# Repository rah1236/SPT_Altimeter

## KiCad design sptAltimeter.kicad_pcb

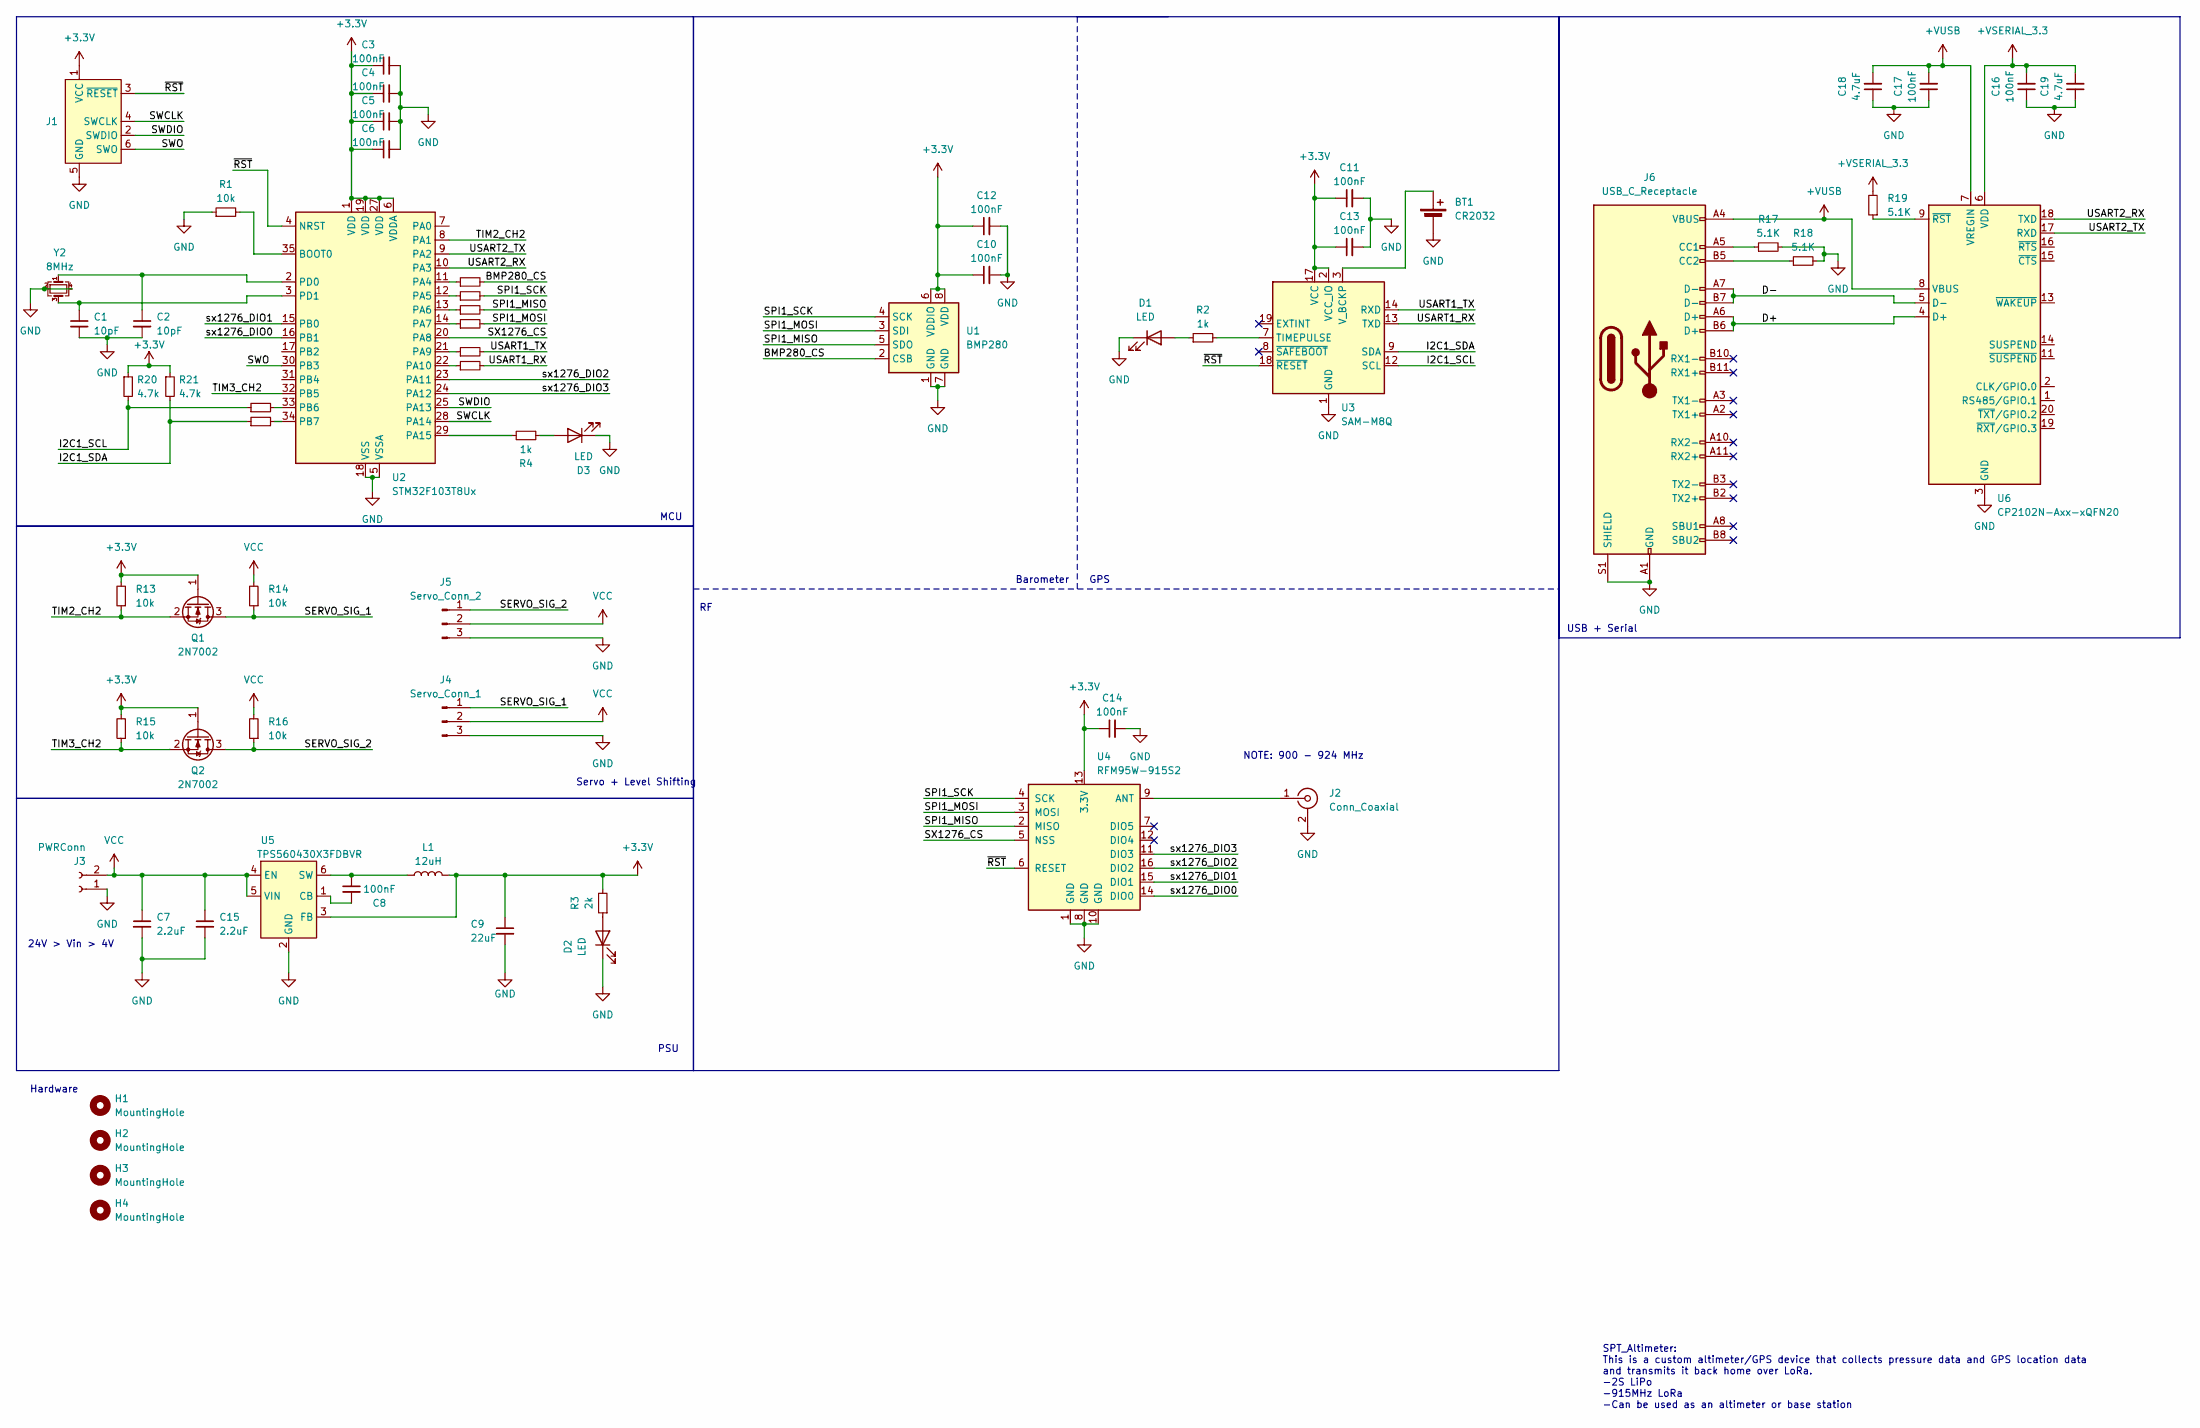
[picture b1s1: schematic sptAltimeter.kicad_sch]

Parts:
BT1: CR2032; BatteryHolder_Keystone_1060_1x2032
C1, C2: 10pF; C_0402_1005Metric; LCSC C650948
C3, C4, C5, C6, C8, C10, C11, C12, C13, C14, C16, C17: 100nF; C_0402_1005Metric
C7, C15: 2.2uF; C_0603_1608Metric
C9: 22uF; C_0402_1005Metric
C18, C19: 4.7uF; C_0402_1005Metric
D1, D2, D3: LED; LED_0603_1608Metric
H1, H2, H3, H4: MountingHole; MountingHole_3.2mm_M3
J1: Conn_ARM_SWD_TagConnect_TC2030-NL; Tag-Connect_TC2030-IDC-NL_2x03_P1.27mm_Vertical
J2: Conn_Coaxial; SMA_Amphenol_132289_EdgeMount
J3: PWRConn; AMASS_XT30PW-M_1x02_P2.50mm_Horizontal
J4: Servo_Conn_1; PinHeader_1x03_P2.54mm_Horizontal
J5: Servo_Conn_2; PinHeader_1x03_P2.54mm_Horizontal
J6: USB_C_Receptacle; USB_C_Receptacle_GCT_USB4105-xx-A_16P_TopMnt_Horizontal
L1: 12uH; L_1210_3225Metric
Q1: 2N7002; SOT-23
Q2: 2N7002; SOT-23; LCSC C3144321
R1, R13, R14, R15, R16: 10k; R_0402_1005Metric
R2, R4: 1k; R_0402_1005Metric
R3: 2k; R_0402_1005Metric
R5, R6, R7, R8, R9, R10, R11, R12: 0; R_0402_1005Metric
R17, R18, R19: 5.1K; R_0603_1608Metric
R20, R21: 4.7k; R_0402_1005Metric
U1: BMP280; Bosch_LGA-8_2x2.5mm_P0.65mm_ClockwisePinNumbering
U2: STM32F103T8Ux; QFN-36-1EP_6x6mm_P0.5mm_EP4.1x4.1mm
U3: SAM-M8Q; ublox_SAM-M8Q
U4: RFM95W-915S2; XCVR_RFM95W-915S2
U5: TPS560430X3FDBVR; SOT-23-6
U6: CP2102N-Axx-xQFN20; SiliconLabs_QFN-20-1EP_3x3mm_P0.5mm_EP1.8x1.8mm
Y2: 8MHz; Crystal_SMD_3225-4Pin_3.2x2.5mm; LCSC C20606311

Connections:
+3.3V: C3.1, C4.1, C5.1, C6.1, C9.1, C10.1, C11.1, C12.1, C13.1, C14.1, J1.1 (VCC), L1.2, Q1.1 (G), Q2.1 (G), R3.2, R13.2, R15.2, R20.1, R21.1, U1.6 (VDDIO), U1.8 (VDD), U2.1 (VDD), U2.6 (VDDA), U2.19 (VDD), U2.27 (VDD), U3.2 (VCC_IO), U3.17 (VCC), U4.13 (3.3V), U5.3 (FB)
+VSERIAL_3.3: C16.2, C19.2, R19.2, U6.6 (VDD)
+VUSB: C17.2, C18.2, J6.A4 (VBUS), J6.A9 (VBUS), J6.B4 (VBUS), J6.B9 (VBUS), U6.7 (VREGIN), U6.8 (VBUS)
/BMP280_CS: R12.2, U1.2 (CSB)
/D+: J6.A6 (D+), J6.B6 (D+), U6.4 (D+)
/D-: J6.A7 (D-), J6.B7 (D-), U6.5 (D-)
/I2C1_SCL: R6.1, R20.2, U3.12 (SCL)
/I2C1_SDA: R5.1, R21.2, U3.9 (SDA)
/SERVO_SIG_1: J4.1, Q1.3 (D), R14.1
/SERVO_SIG_2: J5.1, Q2.3 (D), R16.1
/SPI1_MISO: R10.2, U1.5 (SDO), U4.2 (MISO)
/SPI1_MOSI: R9.2, U1.3 (SDI), U4.3 (MOSI)
/SPI1_SCK: R11.2, U1.4 (SCK), U4.4 (SCK)
/SWCLK: J1.4 (SWCLK), U2.28 (PA14)
/SWDIO: J1.2 (SWDIO), U2.25 (PA13)
/SWO: J1.6 (SWO), U2.30 (PB3)
/SX1276_CS: U2.20 (PA8), U4.5 (NSS)
/TIM2_CH2: Q1.2 (S), R13.1, U2.8 (PA1)
/TIM3_CH2: Q2.2 (S), R15.1, U2.32 (PB5)
/USART1_RX: R7.2, U3.13 (TXD)
/USART1_TX: R8.2, U3.14 (RXD)
/USART2_RX: U2.10 (PA3), U6.18 (TXD)
/USART2_TX: U2.9 (PA2), U6.17 (RXD)
/sx1276_DIO0: U2.16 (PB1), U4.14 (DIO0)
/sx1276_DIO1: U2.15 (PB0), U4.15 (DIO1)
/sx1276_DIO2: U2.23 (PA11), U4.16 (DIO2)
/sx1276_DIO3: U2.24 (PA12), U4.11 (DIO3)
/~RST: J1.3 (~RESET), U2.4 (NRST), U3.18 (~RESET), U4.6 (RESET)
GND: BT1.2 (-), C1.2, C2.2, C3.2, C4.2, C5.2, C6.2, C7.2, C9.2, C10.2, C11.2, C12.2, C13.2, C14.2, C15.2, C16.1, C17.1, C18.1, C19.1, D1.1 (K), D2.1 (K), D3.1 (K), J1.5 (GND), J2.2 (Ext), J3.1, J4.3, J5.3, J6.A1 (GND), J6.A12 (GND), J6.B1 (GND), J6.B12 (GND), J6.S1 (SHIELD), R1.1, R17.2, R18.2, U1.1 (GND), U1.7 (GND), U2.5 (VSSA), U2.18 (VSS), U2.26 (VSS), U2.36 (VSS), U2.37 (VSS), U3.1 (GND), U3.4 (GND), U3.5 (GND), U3.6 (GND), U3.10 (GND), U3.11 (GND), U3.15 (GND), U3.16 (GND), U3.20 (GND), U4.1 (GND), U4.8 (GND), U4.10 (GND), U5.2 (GND), U6.3 (GND), U6.12 (GND), U6.21 (GND), Y2.2, Y2.4
unnamed: BT1.1 (+), U3.3 (V_BCKP)
unnamed: D1.2 (A), R2.1
unnamed: D2.2 (A), R3.1
unnamed: D3.2 (A), R4.1
unnamed: J2.1 (In), U4.9 (ANT)
unnamed: J6.A5 (CC1), R17.1
unnamed: J6.B5 (CC2), R18.1
unnamed: R1.2, U2.35 (BOOT0)
unnamed: R12.1, U2.11 (PA4)
unnamed: R11.1, U2.12 (PA5)
unnamed: R10.1, U2.13 (PA6)
unnamed: R9.1, U2.14 (PA7)
unnamed: R8.1, U2.21 (PA9)
unnamed: R7.1, U2.22 (PA10)
unnamed: R4.2, U2.29 (PA15)
unnamed: R6.2, U2.33 (PB6)
unnamed: R5.2, U2.34 (PB7)
unnamed: C2.1, U2.2 (PD0), Y2.1
unnamed: C1.1, U2.3 (PD1), Y2.3
unnamed: R2.2, U3.7 (TIMEPULSE)
unnamed: C8.2, U5.1 (CB)
unnamed: C8.1, L1.1, U5.6 (SW)
unnamed: R19.1, U6.9 (~RST)
VCC: C7.1, C15.1, J3.2, J4.2, J5.2, R14.2, R16.2, U5.4 (EN), U5.5 (VIN)

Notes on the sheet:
MCU
SPT_Altimeter: This is a custom altimeter/GPS device that collects pressure data and GPS location data and transmits it back home over LoRa. -2S LiPo -915MHz LoRa -Can be used as an altimeter or base station
PSU
24V > Vin > 4V
Barometer
GPS
Servo + Level Shifting
NOTE: 900 - 924 MHz
Hardware
USB + Serial

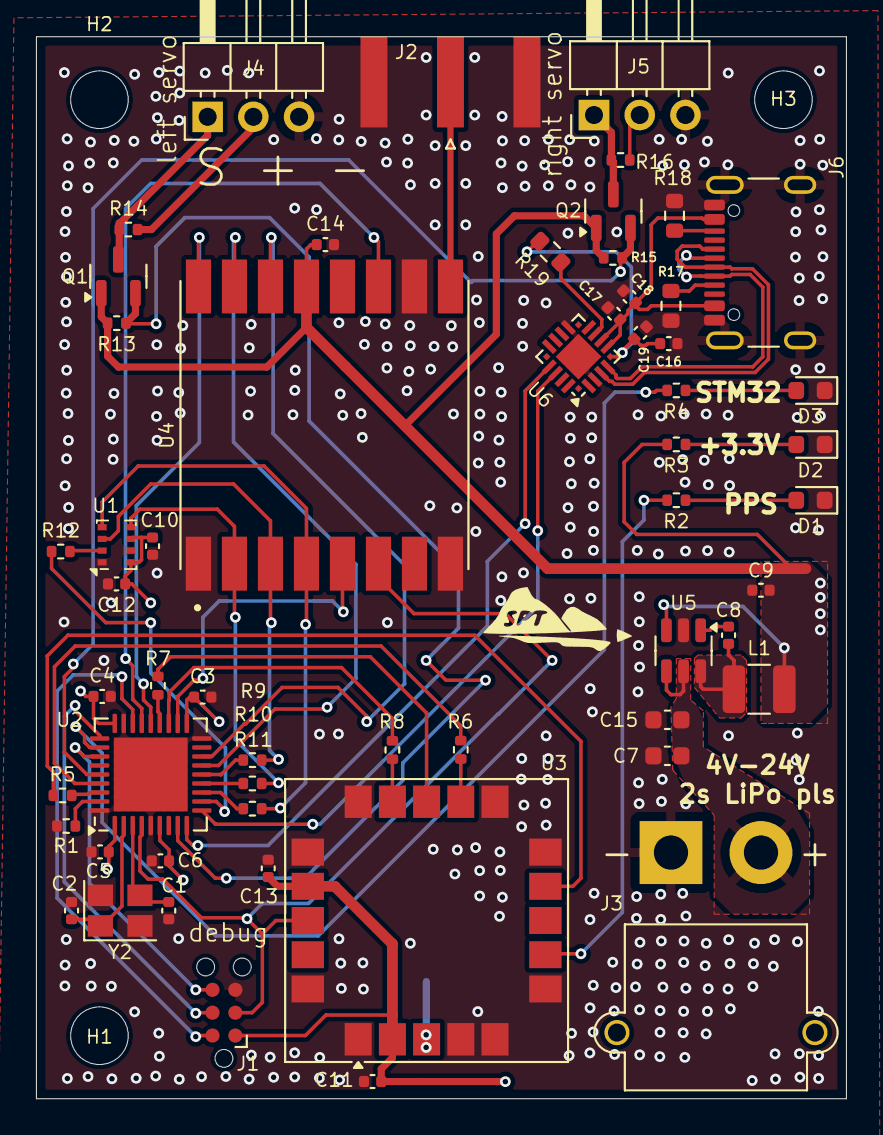
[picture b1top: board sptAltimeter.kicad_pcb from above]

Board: 4 copper layers, 45.0 x 59.0 mm, 61 parts (1 on the bottom side), 53 nets.

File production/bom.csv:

Designator,Footprint,Quantity,Value,LCSC Part #
BT1,BatteryHolder_Keystone_1060_1x2032,1,CR2032,
"C1, C2",0402,2,10pF,C650948
"C10, C11, C12, C13, C14, C16, C17, C3, C4, C5, C6, C8",0402,12,100nF,
"C15, C7",0603,2,2.2uF,
"C18, C19",0402,2,4.7uF,
C9,0402,1,22uF,
"D1, D2, D3",0603,3,LED,
"H1, H2, H3",MountingHole_3.2mm_M3,3,MountingHole,
J2,SMA_Amphenol_132289_EdgeMount,1,Conn_Coaxial,
J3,AMASS_XT30PW-M_1x02_P2.50mm_Horizontal,1,PWRConn,
J4,PinHeader_1x03_P2.54mm_Horizontal,1,Servo_Conn_1,
J5,PinHeader_1x03_P2.54mm_Horizontal,1,Servo_Conn_2,
J6,USB_C_Receptacle_GCT_USB4105-xx-A_16P_TopMnt_Horizontal,1,USB_C_Receptacle,
L1,1210,1,12uH,
"Q1, Q2",SOT-23,2,2N7002,
"R1, R13, R14, R15, R16",0402,5,10k,
"R10, R11, R12, R5, R6, R7, R8, R9",0402,8,0,
"R17, R18, R19",0603,3,5.1K,
"R2, R4",0402,2,1k,
R3,0402,1,2k,
U1,Bosch_LGA-8_2x2.5mm_P0.65mm_ClockwisePinNumbering,1,BMP280,
U2,QFN-36-1EP_6x6mm_P0.5mm_EP4.1x4.1mm,1,STM32F103T8Ux,
U3,ublox_SAM-M8Q,1,SAM-M8Q,
U4,XCVR_RFM95W-915S2,1,RFM95W-915S2,
U5,SOT-23-6,1,TPS560430X3FDBVR,
U6,SiliconLabs_QFN-20-1EP_3x3mm_P0.5mm_EP1.8x1.8mm,1,CP2102N-Axx-xQFN20,
Y2,Crystal_SMD_3225-4Pin_3.2x2.5mm,1,8MHz,C20606311

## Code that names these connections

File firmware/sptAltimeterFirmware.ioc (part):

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Mcu.Name=STM32F103T(8-B)Ux
Mcu.Package=VFQFPN36
Mcu.UserName=STM32F103T8Ux
PA1.Signal=S_TIM2_CH2
PA10.Mode=Asynchronous
PA10.Signal=USART1_RX
PA11.GPIOParameters=GPIO_Label
PA11.GPIO_Label=SX1276_DIO2
PA11.Signal=GPXTI11
PA12.GPIOParameters=GPIO_Label
PA12.GPIO_Label=SX1276_DIO3
PA12.Signal=GPXTI12
PA13.Mode=Serial_Wire
PA13.Signal=SYS_JTMS-SWDIO
PA14.Mode=Serial_Wire
PA14.Signal=SYS_JTCK-SWCLK
PA15.GPIOParameters=GPIO_Label
PA15.GPIO_Label=LED_PIN
PA15.Signal=GPIO_Output
PA2.Mode=Asynchronous
PA2.Signal=USART2_TX
PA3.Mode=Asynchronous
PA3.Signal=USART2_RX
PA4.GPIOParameters=GPIO_Label
PA4.GPIO_Label=BMP280_nCS
PA4.Signal=GPIO_Output
PA5.Mode=Full_Duplex_Master
PA5.Signal=SPI1_SCK
PA6.Mode=Full_Duplex_Master
PA6.Signal=SPI1_MISO
PA7.Mode=Full_Duplex_Master
PA7.Signal=SPI1_MOSI
PA8.GPIOParameters=GPIO_Label
PA8.GPIO_Label=SX1276_nCS
PA8.Signal=GPIO_Output
PA9.Mode=Asynchronous
PA9.Signal=USART1_TX
PB0.GPIOParameters=GPIO_Label
PB0.GPIO_Label=SX1276_DIO0
PB0.Signal=GPXTI0
PB1.GPIOParameters=GPIO_Label
PB1.GPIO_Label=SX1276_DIO1
PB1.Signal=GPXTI1
PB3.Signal=SYS_JTDO-TRACESWO
PB5.Signal=S_TIM3_CH2
PB6.Mode=I2C
PB6.Signal=I2C1_SCL
PB7.Mode=I2C
PB7.Signal=I2C1_SDA
PD0-OSC_IN.Mode=HSE-External-Oscillator
PD0-OSC_IN.Signal=RCC_OSC_IN
PD1-OSC_OUT.Mode=HSE-External-Oscillator
PD1-OSC_OUT.Signal=RCC_OSC_OUT
RCC.SYSCLKFreq_VALUE=16000000
RCC.SYSCLKSource=RCC_SYSCLKSOURCE_PLLCLK
board=custom

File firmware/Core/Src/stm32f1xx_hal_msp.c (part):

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
    __HAL_RCC_GPIOB_CLK_ENABLE();
    /**I2C1 GPIO Configuration
    PB6     ------> I2C1_SCL
    PB7     ------> I2C1_SDA
    */
    GPIO_InitStruct.Pin = GPIO_PIN_6|GPIO_PIN_7;
    GPIO_InitStruct.Mode = GPIO_MODE_AF_OD;
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    __HAL_RCC_I2C1_CLK_DISABLE();

    /**I2C1 GPIO Configuration
    PB6     ------> I2C1_SCL
    PB7     ------> I2C1_SDA
    */
    HAL_GPIO_DeInit(GPIOB, GPIO_PIN_6);

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
    __HAL_RCC_GPIOA_CLK_ENABLE();
    /**SPI1 GPIO Configuration
    PA5     ------> SPI1_SCK
    PA6     ------> SPI1_MISO
    PA7     ------> SPI1_MOSI
    */
    GPIO_InitStruct.Pin = GPIO_PIN_5|GPIO_PIN_7;
    GPIO_InitStruct.Mode = GPIO_MODE_AF_PP;
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    __HAL_RCC_SPI1_CLK_DISABLE();

    /**SPI1 GPIO Configuration
    PA5     ------> SPI1_SCK
    PA6     ------> SPI1_MISO
    PA7     ------> SPI1_MOSI
    */
    HAL_GPIO_DeInit(GPIOA, GPIO_PIN_5|GPIO_PIN_6|GPIO_PIN_7);

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  /* USER CODE END TIM2_MspPostInit 0 */
    __HAL_RCC_GPIOA_CLK_ENABLE();
    /**TIM2 GPIO Configuration
    PA1     ------> TIM2_CH2
    */
    GPIO_InitStruct.Pin = GPIO_PIN_1;
    GPIO_InitStruct.Mode = GPIO_MODE_AF_PP;
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
    __HAL_RCC_GPIOB_CLK_ENABLE();
    /**TIM3 GPIO Configuration
    PB5     ------> TIM3_CH2
    */
    GPIO_InitStruct.Pin = GPIO_PIN_5;
    GPIO_InitStruct.Mode = GPIO_MODE_AF_PP;
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
    __HAL_RCC_GPIOA_CLK_ENABLE();
    /**USART1 GPIO Configuration
    PA9     ------> USART1_TX
    PA10     ------> USART1_RX
    */
    GPIO_InitStruct.Pin = GPIO_PIN_9;
    GPIO_InitStruct.Mode = GPIO_MODE_AF_PP;
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
    __HAL_RCC_GPIOA_CLK_ENABLE();
    /**USART2 GPIO Configuration
    PA2     ------> USART2_TX
    PA3     ------> USART2_RX
    */
    GPIO_InitStruct.Pin = GPIO_PIN_2;
    GPIO_InitStruct.Mode = GPIO_MODE_AF_PP;
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    __HAL_RCC_USART1_CLK_DISABLE();

    /**USART1 GPIO Configuration
    PA9     ------> USART1_TX
    PA10     ------> USART1_RX
    */
    HAL_GPIO_DeInit(GPIOA, GPIO_PIN_9|GPIO_PIN_10);

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    __HAL_RCC_USART2_CLK_DISABLE();

    /**USART2 GPIO Configuration
    PA2     ------> USART2_TX
    PA3     ------> USART2_RX
    */
    HAL_GPIO_DeInit(GPIOA, GPIO_PIN_2|GPIO_PIN_3);

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
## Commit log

2025-01-30 added all files
2025-04-03 Flight config

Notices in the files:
firmware/Core/Src/stm32f1xx_hal_msp.c:
Copyright (c) 2024 STMicroelectronics.
All rights reserved.
This software is licensed under terms that can be found in the LICENSE file
